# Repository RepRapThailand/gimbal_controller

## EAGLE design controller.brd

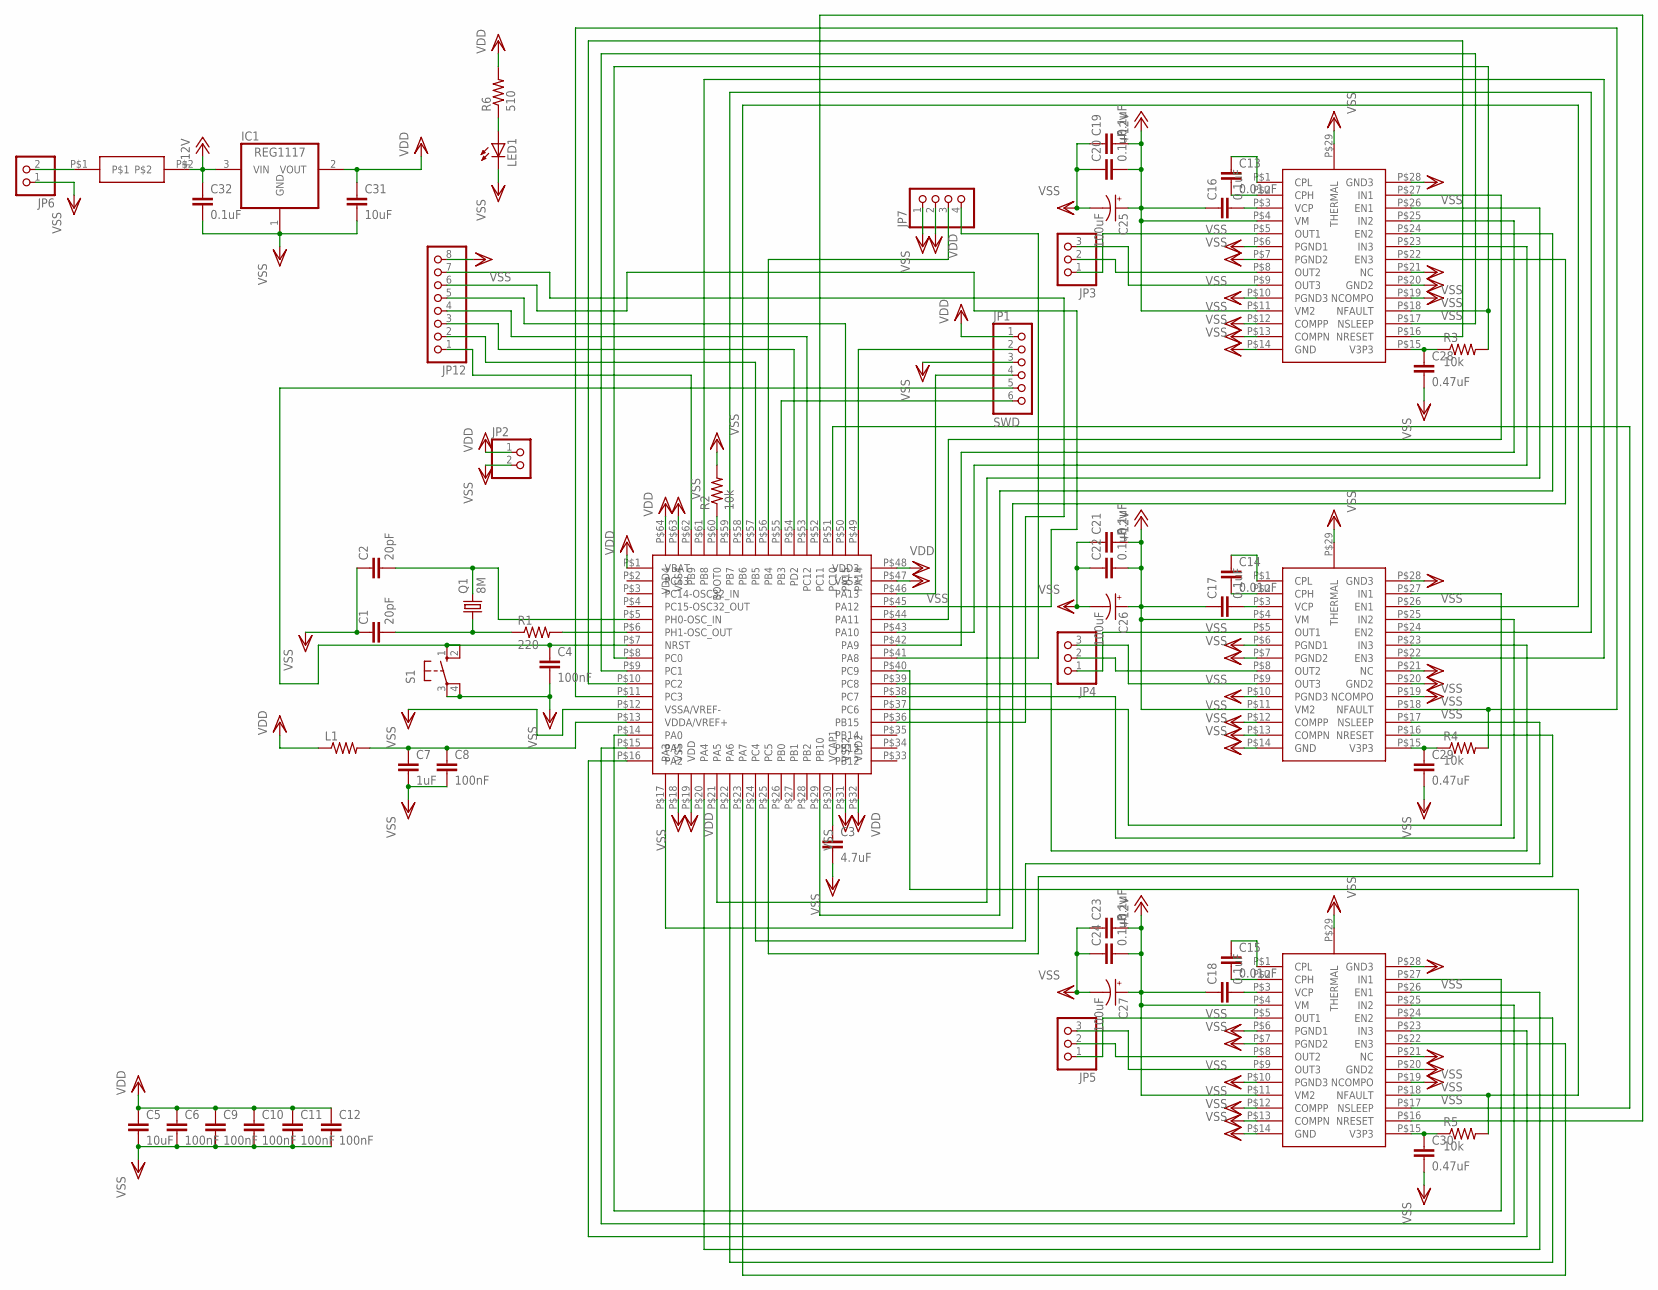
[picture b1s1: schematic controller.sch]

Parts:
C1, C2: 20pF; C0402
C3: 4.7uF; C1206
C4, C6, C8, C9, C10, C11, C12: 100nF; C0402
C5, C31: 10uF; C1206
C7: 1uF; C0603
C13, C14, C15: 0.01uF; C0603
C16, C17, C18, C19, C20, C21, C22, C23, C24: 0.1uF; C0603
C25, C26, C27: 100uF; PANASONIC_D
C28, C29, C30: 0.47uF; C0603
C32: 0.1uF; C1206
IC1: REG1117; SOT223
JP1: SWD; 1X06
JP2, JP6: PINHD-1X2; 1X02
JP3, JP4, JP5: PINHD-1X3; 1X03
JP7: PINHD-1X4; 1X04
JP12: PINHD-1X8; 1X08
L1: R-US_R0603; R0603
LED1: LEDCHIP-LED0603; CHIP-LED0603
Q1: 8M; HC49/S
R1: 220; R0402
R2, R3, R4, R5: 10k; R0402
R6: 510; R0402
S1: 10-XX; B3F-10XX
U$1: STM32F411VET6
U$2, U$3, U$4: DRV8313
U$5: SOD123

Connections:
+12V: C16.1, C17.1, C18.1, C19.2, C20.2, C21.2, C22.2, C23.2, C24.2, C25.+, C26.+, C27.+, C32.1, IC1.3 (VIN), U$2.P$4 (VM), U$2.P$11 (VM2), U$3.P$4 (VM), U$3.P$11 (VM2), U$4.P$4 (VM), U$4.P$11 (VM2), U$5.P$2
unnamed: C2.2, Q1.2, U$1.P$5 (PH0-OSC_IN)
unnamed: C1.2, Q1.1, R1.1
unnamed: R1.2, U$1.P$6 (PH1-OSC_OUT)
unnamed: R2.1, U$1.P$60 (BOOT0)
unnamed: JP1.2, U$1.P$49 (PA14)
unnamed: JP1.4, U$1.P$46 (PA13)
unnamed: C4.1, JP1.5, S1.1 (S), S1.2 (S1), U$1.P$7 (NRST)
unnamed: C3.1, U$1.P$30 (VCAP1)
unnamed: C7.1, C8.1, L1.2, U$1.P$13 (VDDA/VREF+)
unnamed: JP1.6, U$1.P$55 (PB3)
unnamed: JP3.1, U$2.P$5 (OUT1)
unnamed: JP3.2, U$2.P$8 (OUT2)
unnamed: JP3.3, U$2.P$9 (OUT3)
unnamed: JP4.1, U$3.P$5 (OUT1)
unnamed: JP4.2, U$3.P$8 (OUT2)
unnamed: JP4.3, U$3.P$9 (OUT3)
unnamed: JP5.1, U$4.P$5 (OUT1)
unnamed: JP5.2, U$4.P$8 (OUT2)
unnamed: JP5.3, U$4.P$9 (OUT3)
unnamed: C13.1, U$2.P$1 (CPL)
unnamed: C13.2, U$2.P$2 (CPH)
unnamed: C14.1, U$3.P$1 (CPL)
unnamed: C14.2, U$3.P$2 (CPH)
unnamed: C15.1, U$4.P$1 (CPL)
unnamed: C15.2, U$4.P$2 (CPH)
unnamed: C16.2, U$2.P$3 (VCP)
unnamed: C17.2, U$3.P$3 (VCP)
unnamed: C18.2, U$4.P$3 (VCP)
unnamed: R3.2, U$1.P$8 (PC0), U$2.P$18 (NFAULT)
unnamed: C28.1, R3.1, U$2.P$15 (V3P3)
unnamed: C29.1, R4.1, U$3.P$15 (V3P3)
unnamed: R4.2, U$1.P$11 (PC3), U$3.P$18 (NFAULT)
unnamed: R5.2, U$1.P$40 (PC9), U$4.P$18 (NFAULT)
unnamed: C30.1, R5.1, U$4.P$15 (V3P3)
unnamed: U$1.P$44 (PA11), U$2.P$27 (IN1)
unnamed: U$1.P$42 (PA9), U$2.P$25 (IN2)
unnamed: U$1.P$43 (PA10), U$2.P$23 (IN3)
unnamed: U$1.P$21 (PA5), U$2.P$26 (EN1)
unnamed: U$1.P$29 (PB10), U$2.P$24 (EN2)
unnamed: U$1.P$17 (PA3), U$2.P$22 (EN3)
unnamed: U$1.P$37 (PC6), U$3.P$27 (IN1)
unnamed: U$1.P$38 (PC7), U$3.P$25 (IN2)
unnamed: U$1.P$39 (PC8), U$3.P$23 (IN3)
unnamed: U$1.P$58 (PB6), U$3.P$26 (EN1)
unnamed: U$1.P$59 (PB7), U$3.P$24 (EN2)
unnamed: U$1.P$61 (PB8), U$3.P$22 (EN3)
unnamed: U$1.P$16 (PA2), U$4.P$23 (IN3)
unnamed: U$1.P$15 (PA1), U$4.P$25 (IN2)
unnamed: U$1.P$14 (PA0), U$4.P$27 (IN1)
unnamed: U$1.P$20 (PA4), U$4.P$26 (EN1)
unnamed: U$1.P$22 (PA6), U$4.P$24 (EN2)
unnamed: U$1.P$23 (PA7), U$4.P$22 (EN3)
unnamed: U$1.P$9 (PC1), U$2.P$17 (NSLEEP)
unnamed: U$1.P$10 (PC2), U$2.P$16 (NRESET)
unnamed: JP6.2, U$5.P$1
unnamed: U$1.P$24 (PC4), U$3.P$17 (NSLEEP)
unnamed: U$1.P$25 (PC5), U$3.P$16 (NRESET)
unnamed: LED1.A, R6.1
unnamed: U$1.P$51 (PC10), U$4.P$17 (NSLEEP)
unnamed: U$1.P$52 (PC11), U$4.P$16 (NRESET)
unnamed: JP7.3, U$1.P$56 (PB4)
unnamed: JP7.4, U$1.P$41 (PA8)
unnamed: JP12.7, U$1.P$36 (PB15)
unnamed: JP12.6, U$1.P$45 (PA12)
unnamed: JP12.5, U$1.P$50 (PA15)
unnamed: JP12.4, U$1.P$53 (PC12)
unnamed: JP12.3, U$1.P$54 (PD2)
unnamed: JP12.2, U$1.P$57 (PB5)
unnamed: JP12.1, U$1.P$62 (PB9)
VDD: C5.1, C6.1, C9.1, C10.1, C11.1, C12.1, C31.1, IC1.2 (VOUT), JP1.1, JP2.1, JP7.2, L1.1, R6.2, U$1.P$1 (VBAT), U$1.P$19 (VDD), U$1.P$32 (VDD2), U$1.P$48 (VDD3), U$1.P$64 (VDD4)
VSS: C1.1, C2.1, C3.2, C4.2, C5.2, C6.2, C7.2, C8.2, C9.2, C10.2, C11.2, C12.2, C19.1, C20.1, C21.1, C22.1, C23.1, C24.1, C25.-, C26.-, C27.-, C28.2, C29.2, C30.2, C31.2, C32.2, IC1.1 (GND), JP1.3, JP2.2, JP6.1, JP7.1, JP12.8, LED1.C, R2.2, S1.3, S1.4 (P1), U$1.P$12 (VSSA/VREF-), U$1.P$18 (VSS), U$1.P$31 (VSS2), U$1.P$47 (VSS3), U$1.P$63 (VSS4), U$2.P$6 (PGND1), U$2.P$7 (PGND2), U$2.P$10 (PGND3), U$2.P$12 (COMPP), U$2.P$13 (COMPN), U$2.P$14 (GND), U$2.P$19 (NCOMPO), U$2.P$20 (GND2), U$2.P$21 (NC), U$2.P$28 (GND3), U$2.P$29 (THERMAL), U$3.P$6 (PGND1), U$3.P$7 (PGND2), U$3.P$10 (PGND3), U$3.P$12 (COMPP), U$3.P$13 (COMPN), U$3.P$14 (GND), U$3.P$19 (NCOMPO), U$3.P$20 (GND2), U$3.P$21 (NC), U$3.P$28 (GND3), U$3.P$29 (THERMAL), U$4.P$6 (PGND1), U$4.P$7 (PGND2), U$4.P$10 (PGND3), U$4.P$12 (COMPP), U$4.P$13 (COMPN), U$4.P$14 (GND), U$4.P$19 (NCOMPO), U$4.P$20 (GND2), U$4.P$21 (NC), U$4.P$28 (GND3), U$4.P$29 (THERMAL)

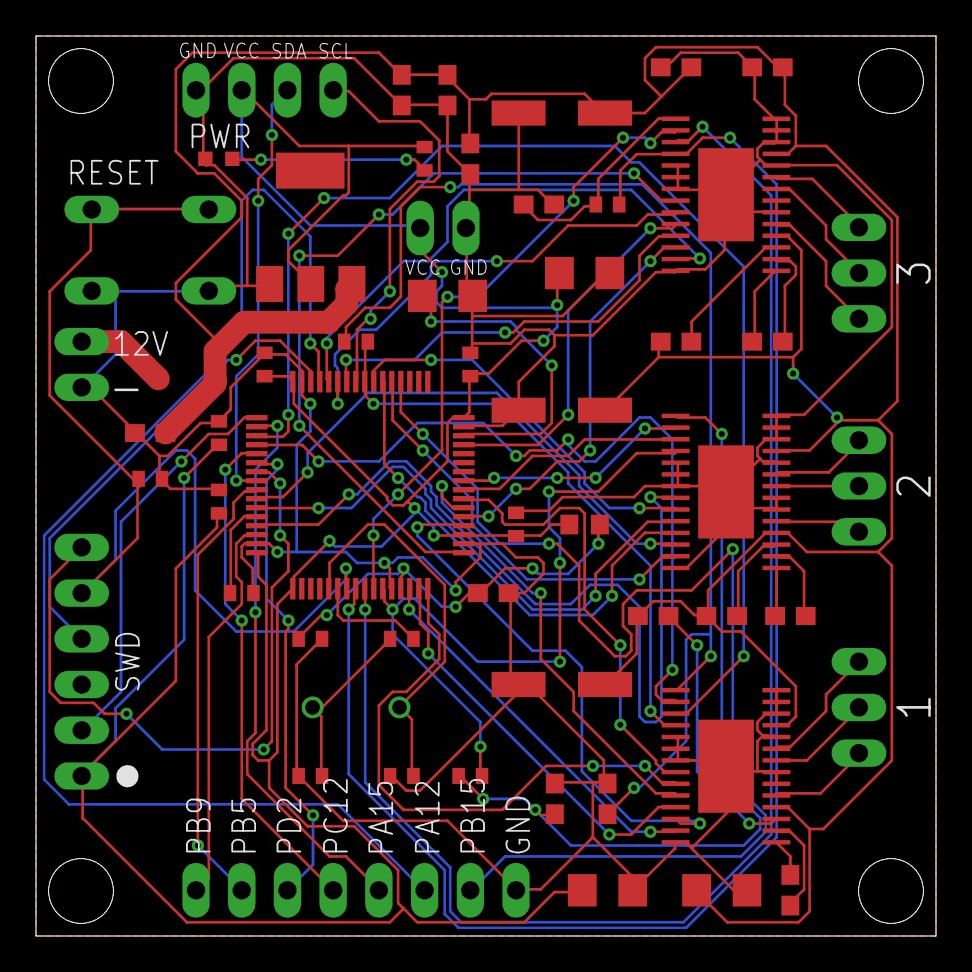
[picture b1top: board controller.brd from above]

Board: 2 copper layers, 50.0 x 50.0 mm, 56 parts (0 on the bottom side), 72 nets.

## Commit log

2017-02-16 Added image of board
